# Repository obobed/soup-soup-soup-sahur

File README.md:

# 3SS
A custom pcb badge for Fallout with a smoky twist (a button that releases the magic smoke)! made by @obob on [Slack](https://hackclub.enterprise.slack.com/team/U092DB4LGMP)

## PCB

## Schema

## 3D 

## BOM
|Item              |LCSC Part #|Cost (total)|Notes                                          |FIELD5|FIELD6|FIELD7|FIELD8|
|------------------|-----------|------------|-----------------------------------------------|------|------|------|------|
|Switch            |           |            |From venue                                     |      |      |      |      |
|USB-C 12 pin      |           |            |Purchased by myself previously at HQB yesterday|      |      |      |      |
|220uF capactior   |C5378      |0.65        |MOQ 50                                         |      |      |      |      |
|Blue LEDs         |C2288      |0.52        |MOQ 50                                         |      |      |      |      |
|47 ohm resistor   |C140087    |0.3         |MOQ 100                                        |      |      |      |      |
|18 ohm resistor   |C70810     |0.42        |MOQ 50, Magic Smoke                            |      |      |      |      |
|5.1k ohm resistor |C2907044   |0.28        |MOQ 100                                        |      |      |      |      |
|NXP NT3H2111W0FHKH|C710403    |3.77        |MOQ 5, NFC Chip                                |      |      |      |      |
|                  |           |            |                                               |      |      |      |      |
|Total             |           |5.94        |                                               |      |      |      |      |

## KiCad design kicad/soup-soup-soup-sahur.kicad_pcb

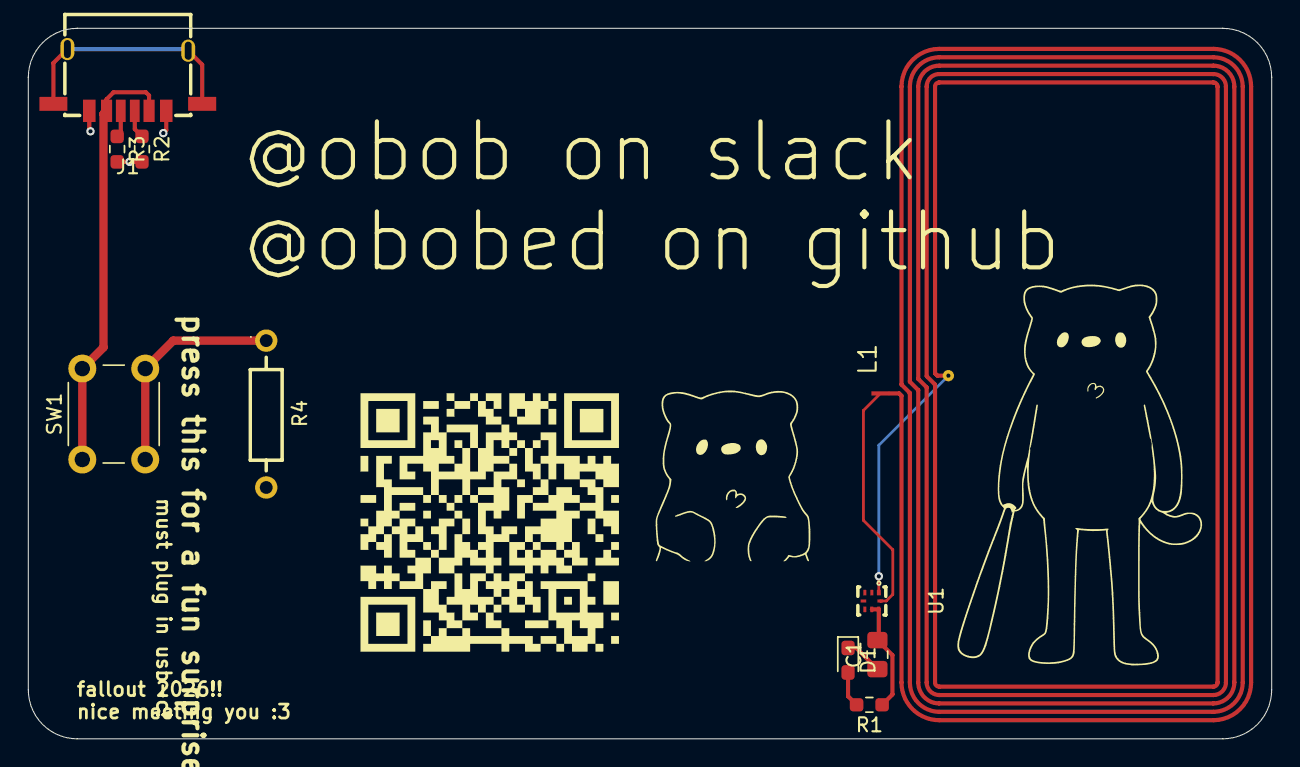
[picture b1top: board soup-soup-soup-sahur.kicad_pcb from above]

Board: 2 copper layers, 88.9 x 50.8 mm, 10 parts (0 on the bottom side), 8 nets.

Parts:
C1: 220; C_0805_2012Metric_Pad1.18x1.45mm_HandSolder
D1: BLUE; LED_0603_1608Metric_Pad1.05x0.95mm_HandSolder
J1: USB_C_Receptacle_PowerOnly_24P; USB-C-SMD_USB-TYPE-C-006
L1: L; 25X48MM_NFC_ANTENNA
R1: 47; R_0603_1608Metric_Pad0.98x0.95mm_HandSolder
R2, R3: 5k1; R_0603_1608Metric_Pad0.98x0.95mm_HandSolder
R4: 18; RES-TH_BD2.2-L6.5-P10.50-D0.6
SW1: SW_Push; SW_PUSH_6mm
U1: NT3H2111W0FHKH; XQFN-8_L1.6-W1.6-P0.50-BL_NT3H2111W0FHKH

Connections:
GND: J1.A12 (GND), J1.B12 (GND), R2.2, R3.2, R4.2
unnamed: D1.2 (A), R1.2
unnamed: C1.1, D1.1 (K), U1.2 (VSS)
unnamed: J1.A5 (CC1), R2.1
unnamed: J1.B5 (CC2), R3.1
unnamed: R4.1, SW1.2
unnamed: C1.2, R1.1, U1.6 (VCC), U1.7 (VOUT)
VBUS: J1.A9 (VBUS), J1.B9 (VBUS), SW1.1
